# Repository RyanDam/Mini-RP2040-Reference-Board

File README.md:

# RP2040 Reference board

Tiny RP2040 Reference board for development

## Schematic

## Ordering PCB

Use `Production/rp2040ref_r1.2.zip` file to order PCB.

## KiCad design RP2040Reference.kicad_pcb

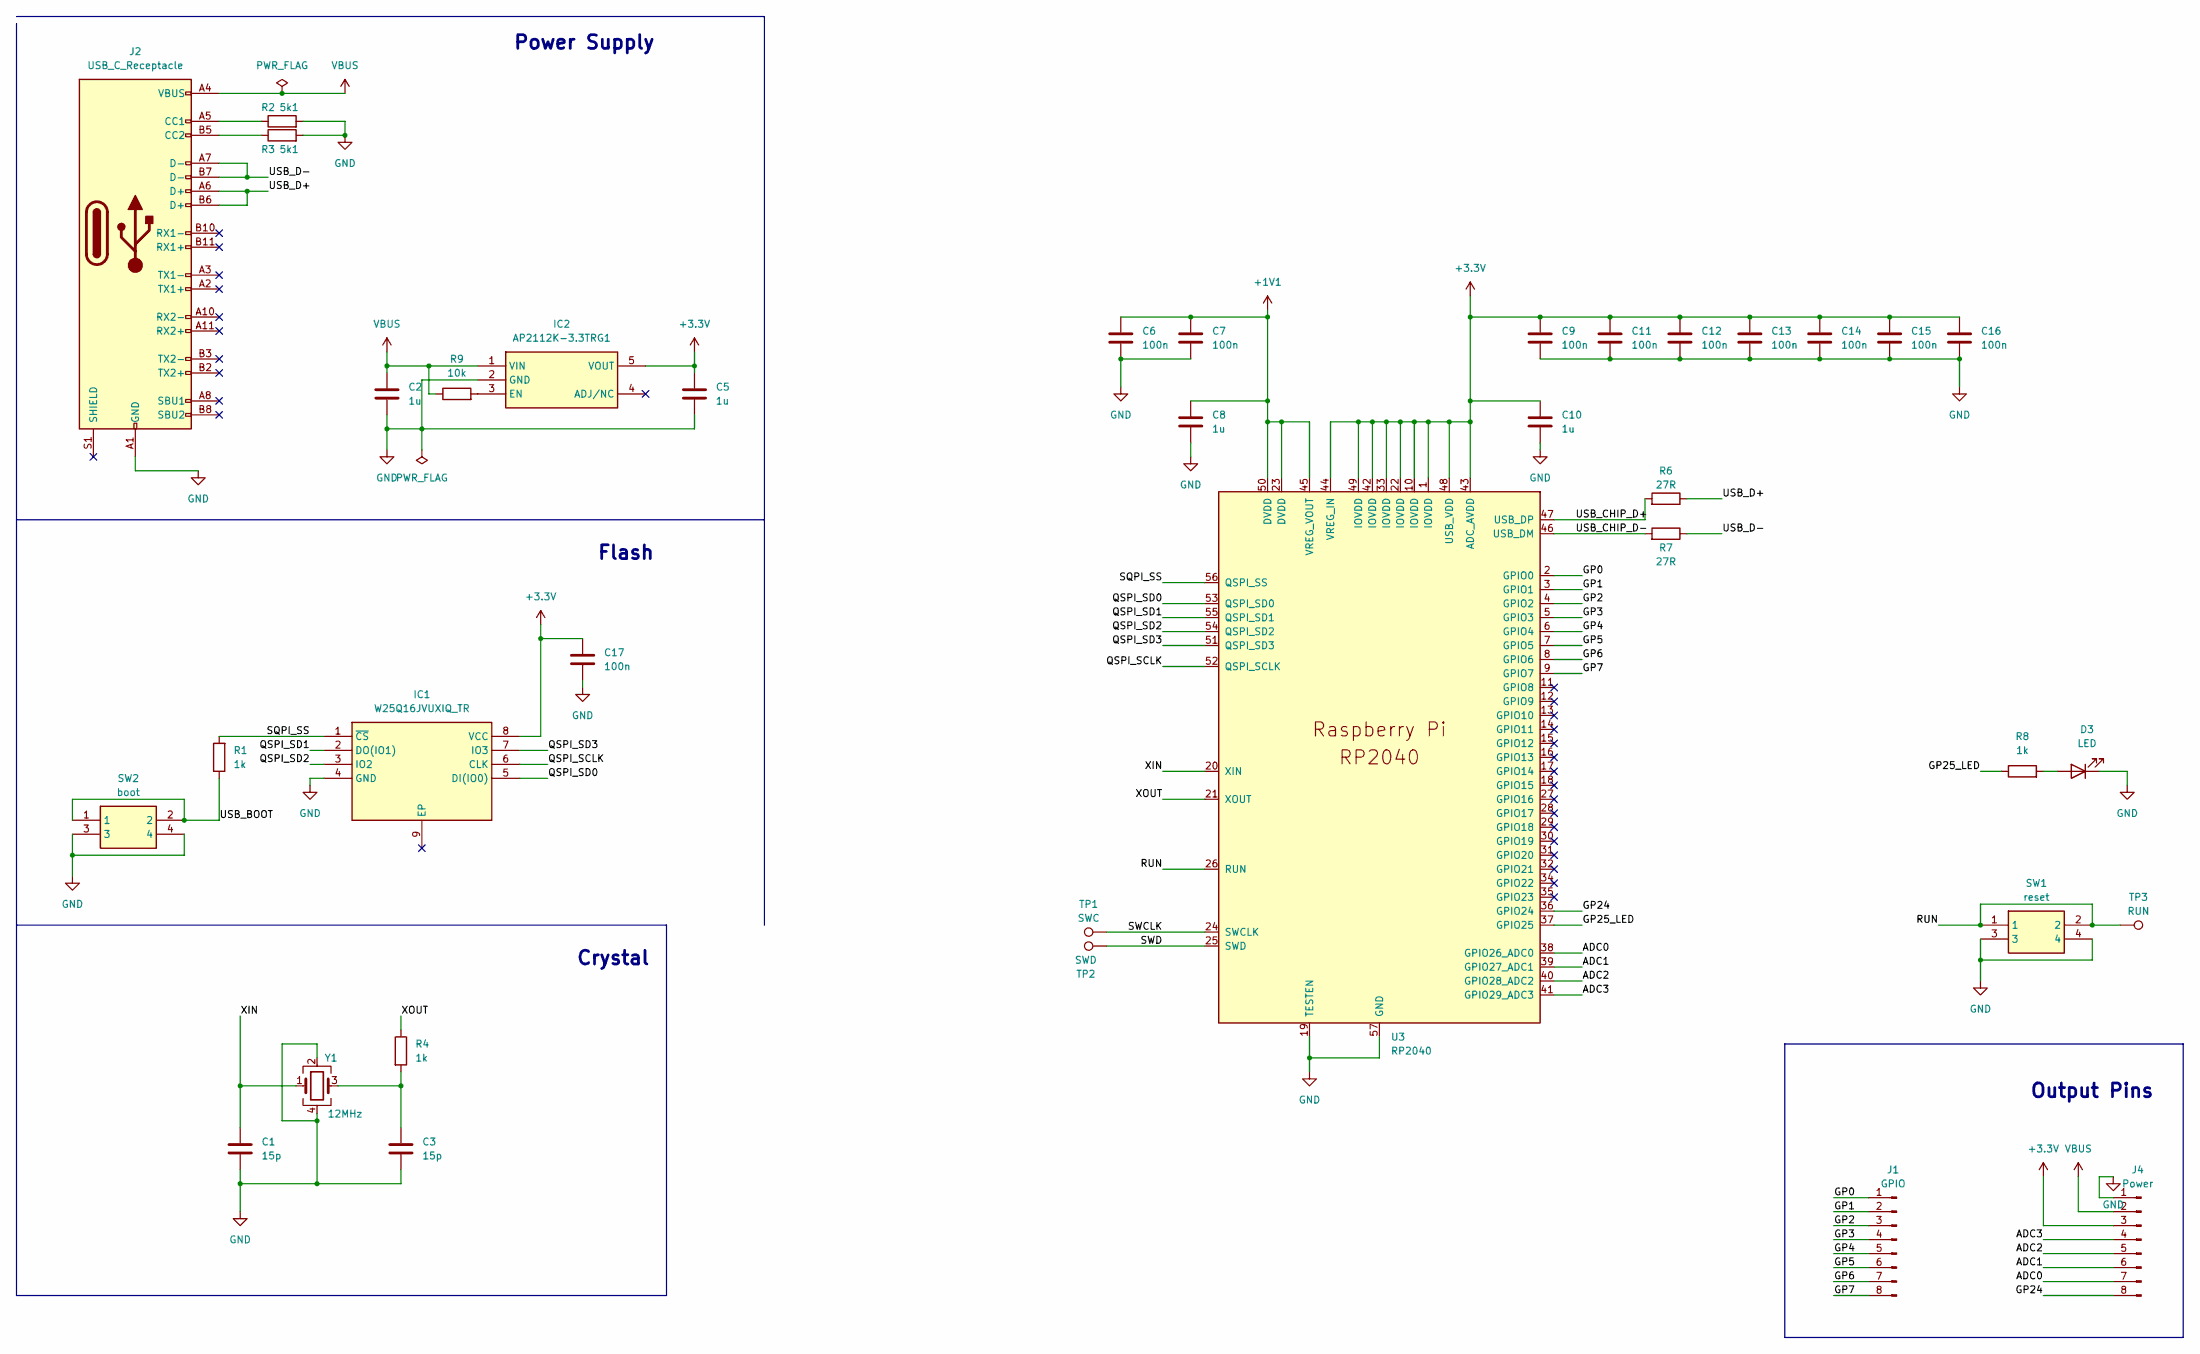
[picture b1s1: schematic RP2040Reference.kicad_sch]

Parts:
C1, C3: 15p; C_0402_1005Metric_Pad0.74x0.62mm_HandSolder; LCSC_Part_Number C326803
C2, C5, C8, C10: 1u; C_0402_1005Metric_Pad0.74x0.62mm_HandSolder; LCSC_Part_Number C14445
C6, C7, C9, C11, C12, C13, C14, C15, C16, C17: 100n; C_0402_1005Metric_Pad0.74x0.62mm_HandSolder; LCSC_Part_Number C541464
D3: LED; LED_0402_1005Metric_Pad0.77x0.64mm_HandSolder; LCSC_Part_Number C434449
IC1: W25Q16JVUXIQ_TR; SON50P300X200X60-9N; Mouser Part Number 454-W25Q16JVUXIQTR
IC2: AP2112K-3.3TRG1; SOT95P282X130-5N; Mouser Part Number 621-AP2112K-3.3TRG1
J1: GPIO; PinHeader_1x08_P2.54mm_Vertical
J2: USB_C_Receptacle; USB_C_Receptacle_HRO_TYPE-C-31-M-12; LCSC_Part_Number C165948
J4: Power; PinHeader_1x08_P2.54mm_Vertical
R1, R4, R8: 1k; R_0402_1005Metric_Pad0.72x0.64mm_HandSolder; LCSC_Part_Number C11702
R2, R3: 5k1; R_0402_1005Metric_Pad0.72x0.64mm_HandSolder; LCSC_Part_Number C25905
R6, R7: 27R; R_0402_1005Metric_Pad0.72x0.64mm_HandSolder; LCSC_Part_Number C138021
R9: 10k; R_0402_1005Metric_Pad0.72x0.64mm_HandSolder; LCSC_Part_Number C25744
SW1: reset; SMT_4.2X3.2_; Mouser Part Number 688-SKRPACE010
SW2: boot; SMT_4.2X3.2_; Mouser Part Number 688-SKRPACE010
TP1: SWC; TestPoint_Pad_D1.5mm
TP2: SWD; TestPoint_Pad_D1.5mm
TP3: RUN; TestPoint_Pad_D1.5mm
U3: RP2040; RP2040-QFN-56; LCSC_Part_Number C2040
Y1: 12MHz; Crystal_SMD_3225-4Pin_3.2x2.5mm; LCSC_Part_Number C5765982

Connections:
+1V1: C6.1, C7.1, C8.1, U3.23 (DVDD), U3.45 (VREG_VOUT), U3.50 (DVDD)
+3.3V: C5.1, C9.1, C10.1, C11.1, C12.1, C13.1, C14.1, C15.1, C16.1, C17.1, IC1.8 (VCC), IC2.5 (VOUT), J4.3, U3.1 (IOVDD), U3.10 (IOVDD), U3.22 (IOVDD), U3.33 (IOVDD), U3.42 (IOVDD), U3.43 (ADC_AVDD), U3.44 (VREG_IN), U3.48 (USB_VDD), U3.49 (IOVDD)
/ADC0: J4.7, U3.38 (GPIO26_ADC0)
/ADC1: J4.6, U3.39 (GPIO27_ADC1)
/ADC2: J4.5, U3.40 (GPIO28_ADC2)
/ADC3: J4.4, U3.41 (GPIO29_ADC3)
/GP0: J1.1, U3.2 (GPIO0)
/GP1: J1.2, U3.3 (GPIO1)
/GP2: J1.3, U3.4 (GPIO2)
/GP3: J1.4, U3.5 (GPIO3)
/GP4: J1.5, U3.6 (GPIO4)
/GP5: J1.6, U3.7 (GPIO5)
/GP6: J1.7, U3.8 (GPIO6)
/GP7: J1.8, U3.9 (GPIO7)
/GP24: J4.8, U3.36 (GPIO24)
/GP25_LED: R8.1, U3.37 (GPIO25)
/QSPI_SCLK: IC1.6 (CLK), U3.52 (QSPI_SCLK)
/QSPI_SD0: IC1.5 (DI(IO0)), U3.53 (QSPI_SD0)
/QSPI_SD1: IC1.2 (DO(IO1)), U3.55 (QSPI_SD1)
/QSPI_SD2: IC1.3 (IO2), U3.54 (QSPI_SD2)
/QSPI_SD3: IC1.7 (IO3), U3.51 (QSPI_SD3)
/RUN: SW1.1, SW1.2, TP3.1, U3.26 (RUN)
/SQPI_SS: IC1.1 (~CS), R1.2, U3.56 (QSPI_SS)
/SWCLK: TP1.1, U3.24 (SWCLK)
/SWD: TP2.1, U3.25 (SWD)
/USB_BOOT: R1.1, SW2.1, SW2.2
/USB_CHIP_D+: R6.2, U3.47 (USB_DP)
/USB_CHIP_D-: R7.2, U3.46 (USB_DM)
/USB_D+: J2.A6 (D+), J2.B6 (D+), R6.1
/USB_D-: J2.A7 (D-), J2.B7 (D-), R7.1
/XIN: C1.1, U3.20 (XIN), Y1.1
/XOUT: R4.1, U3.21 (XOUT)
GND: C1.2, C2.2, C3.2, C5.2, C6.2, C7.2, C8.2, C9.2, C10.2, C11.2, C12.2, C13.2, C14.2, C15.2, C16.2, C17.2, D3.1 (K), IC1.4 (GND), IC2.2 (GND), J2.A1 (GND), J2.A12 (GND), J2.B1 (GND), J2.B12 (GND), J4.1, R2.2, R3.2, SW1.3, SW1.4, SW2.3, SW2.4, U3.19 (TESTEN), U3.57 (GND), Y1.2, Y1.4
unnamed: C3.1, R4.2, Y1.3
unnamed: D3.2 (A), R8.2
unnamed: IC2.3 (EN), R9.2
unnamed: J2.A5 (CC1), R2.1
unnamed: J2.B5 (CC2), R3.1
VBUS: C2.1, IC2.1 (VIN), J2.A4 (VBUS), J2.A9 (VBUS), J2.B4 (VBUS), J2.B9 (VBUS), J4.2, R9.1

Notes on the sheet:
Power Supply
Flash
Output Pins
Crystal

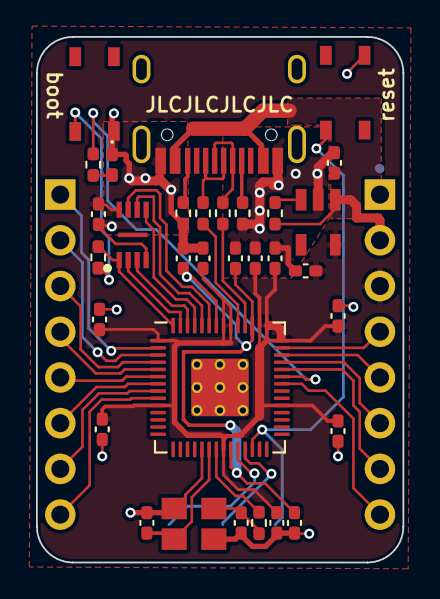
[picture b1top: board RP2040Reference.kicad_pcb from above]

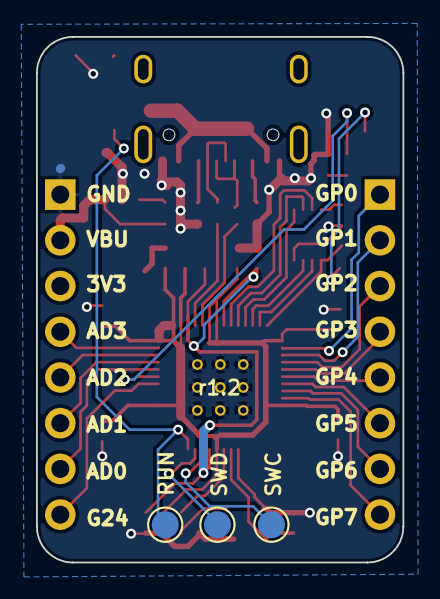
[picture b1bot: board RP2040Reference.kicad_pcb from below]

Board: 2 copper layers, 20.4 x 29.2 mm, 37 parts (3 on the bottom side), 39 nets.

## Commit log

2023-10-25 init commit
